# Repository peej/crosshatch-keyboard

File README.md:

# Crosshatch - Through-hole ortholinear 60% keyboard PCB

Crosshatch is a 12 column ortholinear keyboard PCB using through-hole components only.

The goal of this project is to build an all through-hole component ortholinear PCB that fits in a standard 60% tray mount case.

Inspired by the [Plaid keyboard](https://github.com/hsgw/plaid).

* Designed to be easy to build with minimal soldering experience.
* All through-hole components, no SMD soldering required.
* Get that visible component aesthetic in a standard 60% tray-mount case.
* Plateless.

# Bill of Materials (BOM)

|Ref|num||
| :- |  :- |  :- | 
|C1,C2|2|multilayer ceramic capacitor 22pF or 20pF|
|C3|1|electrolytic capacitor 10uF|
|C4,C5|2|multilayer ceramic capacitor 0.1uF|
|D1-60|60|diode 1n4148|
|D66,D67|2|zener diode 3.6V|
|F1|1|polyfuse 100mA|
|J1|1|USB miniB connector Omron XM7D-0512 or equivalent|
|J2|1|2x3 pin header|
|LED1|1|3mm LED red|
|MX1-60|60|MX PCB mount (5 pin) keyboard switch|
|R1,R7|3|resistor 1.5kΩ|
|R2,R3|2|resistor 75Ω|
|R4|1|resistor 10kΩ|
|SW50,SW51|2|tactile switch|
|U1|1|ATMEGA328P|
|Y1|1|crystal 16MHz|
|PCB|1||
|stabilizer|0-2|switch stabilizer for optional 2u keys|
|cover|1|acrylic component cover|
|screw|8|M2 8mm|
|standoff|4|M2 10mm|

# Ordering PCBs

PCBs can be manufactuered by a variety of online PCB fabricators. You can use [PCBShopper](https://pcbshopper.com/) to search for the best price.

The zip file in the gerber directory contains the gerber files your fabricator will need to make the PCB [lumberjack.zip](https://github.com/peej/crosshatch-keyboard/blob/master/gerber/crosshatch.zip) PCB.

When uploading the gerber zip files, use the default PCB settings.

# Construction

TBD

# Bootloader

TBD

# Firmware

TBD

# Component cover

95x38mm 2mm thick acrylic

TBD

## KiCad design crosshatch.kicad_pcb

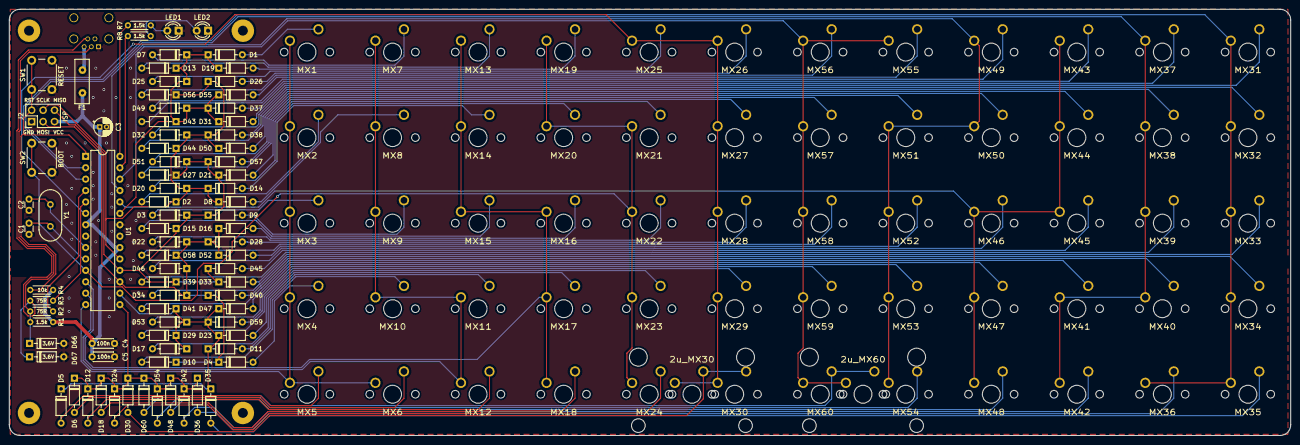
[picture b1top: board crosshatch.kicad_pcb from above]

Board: 2 copper layers, 285.4 x 94.9 mm, 150 parts (1 on the bottom side), 90 nets.

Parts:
2u_MX30, 2u_MX60: SW_Push; MX_PCB_200B
C1, C2: 22p; C_Disc_D3.0mm_W1.6mm_P2.50mm
C3: 4.7u; CP_Radial_D4.0mm_P1.50mm
C4, C5: 100n; C_Disc_D4.3mm_W1.9mm_P5.00mm
D1, D2, D3, D4, D5, D6, D7, D8, D9, D10, D11, D12, D13, D14, D15, D16, D17, D18, D19, D20, D21, D22, D23, D24, D25, D26, D27, D28, D29, D30, D31, D32, D33, D34, D35, D36, D37, D38, D39, D40, D41, D42, D43, D44, D45, D46, D47, D48, D49, D50, D51, D52, D53, D54, D55, D56, D57, D58, D59, D60: 1N4148; D_DO-35_SOD27_P7.62mm_Horizontal
D66, D67: 3.6V; D_DO-35_SOD27_P7.62mm_Horizontal
F1: 100mA; Fuse_Bourns_MF-RHT100
H1, H2, H3, H4: M2; MountingHole_M2
H5, H6: M2; MountingSlot_M2
J1: USB_OTG; USB_Mini-B
J2: AVR_ISP_6; PinHeader_2x03_P2.54mm_Vertical
LED1: RED; LED_D3.0mm
LED2: GREEN; LED_D3.0mm
MX1, MX2, MX3, MX4, MX5, MX6, MX7, MX8, MX9, MX10, MX11, MX12, MX13, MX14, MX15, MX16, MX17, MX18, MX19, MX20, MX21, MX22, MX23, MX24, MX25, MX26, MX27, MX28, MX29, MX30, MX31, MX32, MX33, MX34, MX35, MX36, MX37, MX38, MX39, MX40, MX41, MX42, MX43, MX44, MX45, MX46, MX47, MX48, MX49, MX50, MX51, MX52, MX53, MX54, MX55, MX56, MX57, MX58, MX59, MX60: SW_Push; MX
R1, R7, R8: 1.5k; R_Axial_DIN0204_L3.6mm_D1.6mm_P5.08mm_Horizontal
R2, R3: 75R; R_Axial_DIN0204_L3.6mm_D1.6mm_P5.08mm_Horizontal
R4: 10k; R_Axial_DIN0204_L3.6mm_D1.6mm_P5.08mm_Horizontal
SW1: RESET; SW_PUSH_6mm
SW2: BOOT; SW_PUSH_6mm
U1: ATMEGA328-PU; DIP-28_W7.62mm
Y1: 16MHz; Crystal_HC49-4H_Vertical

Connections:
+5V: C3.1, C4.1, C5.1, F1.2, J2.5, R1.2, R4.1, U1.7, U1.20
/COL0: MX1.2, MX2.2, MX3.2, MX4.2, MX5.2, MX6.2, U1.14
/COL1: MX7.2, MX8.2, MX9.2, MX10.2, MX11.2, MX12.2, U1.13
/COL2: MX13.2, MX14.2, MX15.2, MX16.2, MX17.2, MX18.2, U1.12
/COL3: MX19.2, MX20.2, MX21.2, MX22.2, MX23.2, MX24.2, SW2.1, U1.11
/COL4: 2u_MX30.2, MX25.2, MX26.2, MX27.2, MX28.2, MX29.2, MX30.2, U1.6
/COL5: MX31.2, MX32.2, MX33.2, MX34.2, MX35.2, MX36.2, U1.3
/COL6: MX37.2, MX38.2, MX39.2, MX40.2, MX41.2, MX42.2, U1.2
/COL7: MX43.2, MX44.2, MX45.2, MX46.2, MX47.2, MX48.2, U1.24
/COL8: MX49.2, MX50.2, MX51.2, MX52.2, MX53.2, MX54.2, U1.25
/COL9: 2u_MX60.2, MX55.2, MX56.2, MX57.2, MX58.2, MX59.2, MX60.2, U1.26
/LED1: R7.1, U1.28
/LED2: R8.1, U1.27
/RESET: J2.2, R4.2, SW1.1, U1.1
/ROW0: D1.1, D7.1, D13.1, D19.1, D25.1, D31.1, D37.1, D43.1, D49.1, D55.1, U1.23
/ROW1: D2.1, D8.1, D14.1, D20.1, D26.1, D32.1, D38.1, D44.1, D50.1, D56.1, J2.4, U1.19
/ROW2: D3.1, D9.1, D15.1, D21.1, D27.1, D33.1, D39.1, D45.1, D51.1, D57.1, J2.6, U1.18
/ROW3: D4.1, D10.1, D16.1, D22.1, D28.1, D34.1, D40.1, D46.1, D52.1, D58.1, J2.3, U1.17
/ROW4: D5.1, D11.1, D17.1, D23.1, D29.1, D35.1, D41.1, D47.1, D53.1, D59.1, U1.16
/ROW5: D6.1, D12.1, D18.1, D24.1, D30.1, D36.1, D42.1, D48.1, D54.1, D60.1, U1.15
/USB_D+: R2.1, U1.4
/USB_D-: R3.1, U1.5
GND: C1.2, C2.2, C3.2, C4.2, C5.2, D66.2, D67.2, J1.5, J2.1, LED1.1, LED2.1, SW1.2, SW2.2, U1.8, U1.22
unnamed: 2u_MX30.1, D30.2, MX30.1
unnamed: 2u_MX60.1, D60.2, MX60.1
unnamed: C1.1, U1.10, Y1.2
unnamed: C2.1, U1.9, Y1.1
unnamed: D1.2, MX1.1
unnamed: D2.2, MX2.1
unnamed: D3.2, MX3.1
unnamed: D4.2, MX4.1
unnamed: D5.2, MX5.1
unnamed: D6.2, MX6.1
unnamed: D7.2, MX7.1
unnamed: D8.2, MX8.1
unnamed: D9.2, MX9.1
unnamed: D10.2, MX10.1
unnamed: D11.2, MX11.1
unnamed: D12.2, MX12.1
unnamed: D13.2, MX13.1
unnamed: D14.2, MX14.1
unnamed: D15.2, MX15.1
unnamed: D16.2, MX16.1
unnamed: D17.2, MX17.1
unnamed: D18.2, MX18.1
unnamed: D19.2, MX19.1
unnamed: D20.2, MX20.1
unnamed: D21.2, MX21.1
unnamed: D22.2, MX22.1
unnamed: D23.2, MX23.1
unnamed: D24.2, MX24.1
unnamed: D25.2, MX25.1
unnamed: D26.2, MX26.1
unnamed: D27.2, MX27.1
unnamed: D28.2, MX28.1
unnamed: D29.2, MX29.1
unnamed: D31.2, MX31.1
unnamed: D32.2, MX32.1
unnamed: D33.2, MX33.1
unnamed: D34.2, MX34.1
unnamed: D35.2, MX35.1
unnamed: D36.2, MX36.1
unnamed: D37.2, MX37.1
unnamed: D38.2, MX38.1
unnamed: D39.2, MX39.1
unnamed: D40.2, MX40.1
unnamed: D41.2, MX41.1
unnamed: D42.2, MX42.1
unnamed: D43.2, MX43.1
unnamed: D44.2, MX44.1
unnamed: D45.2, MX45.1
unnamed: D46.2, MX46.1
unnamed: D47.2, MX47.1
unnamed: D48.2, MX48.1
unnamed: D49.2, MX49.1
unnamed: D50.2, MX50.1
unnamed: D51.2, MX51.1
unnamed: D52.2, MX52.1
unnamed: D53.2, MX53.1
unnamed: D54.2, MX54.1
unnamed: D55.2, MX55.1
unnamed: D56.2, MX56.1
unnamed: D57.2, MX57.1
unnamed: D58.2, MX58.1
unnamed: D59.2, MX59.1
unnamed: D66.1, J1.3, R1.1, R2.2
unnamed: D67.1, J1.2, R3.2
unnamed: F1.1, J1.1
unnamed: LED1.2, R7.2
unnamed: LED2.2, R8.2

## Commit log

2020-12-11 Add gerbers
2020-12-11 Add basic readme file
